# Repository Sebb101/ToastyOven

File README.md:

# ToastyOven
Custom PCBA Reflow Oven made from consumer toaster oven

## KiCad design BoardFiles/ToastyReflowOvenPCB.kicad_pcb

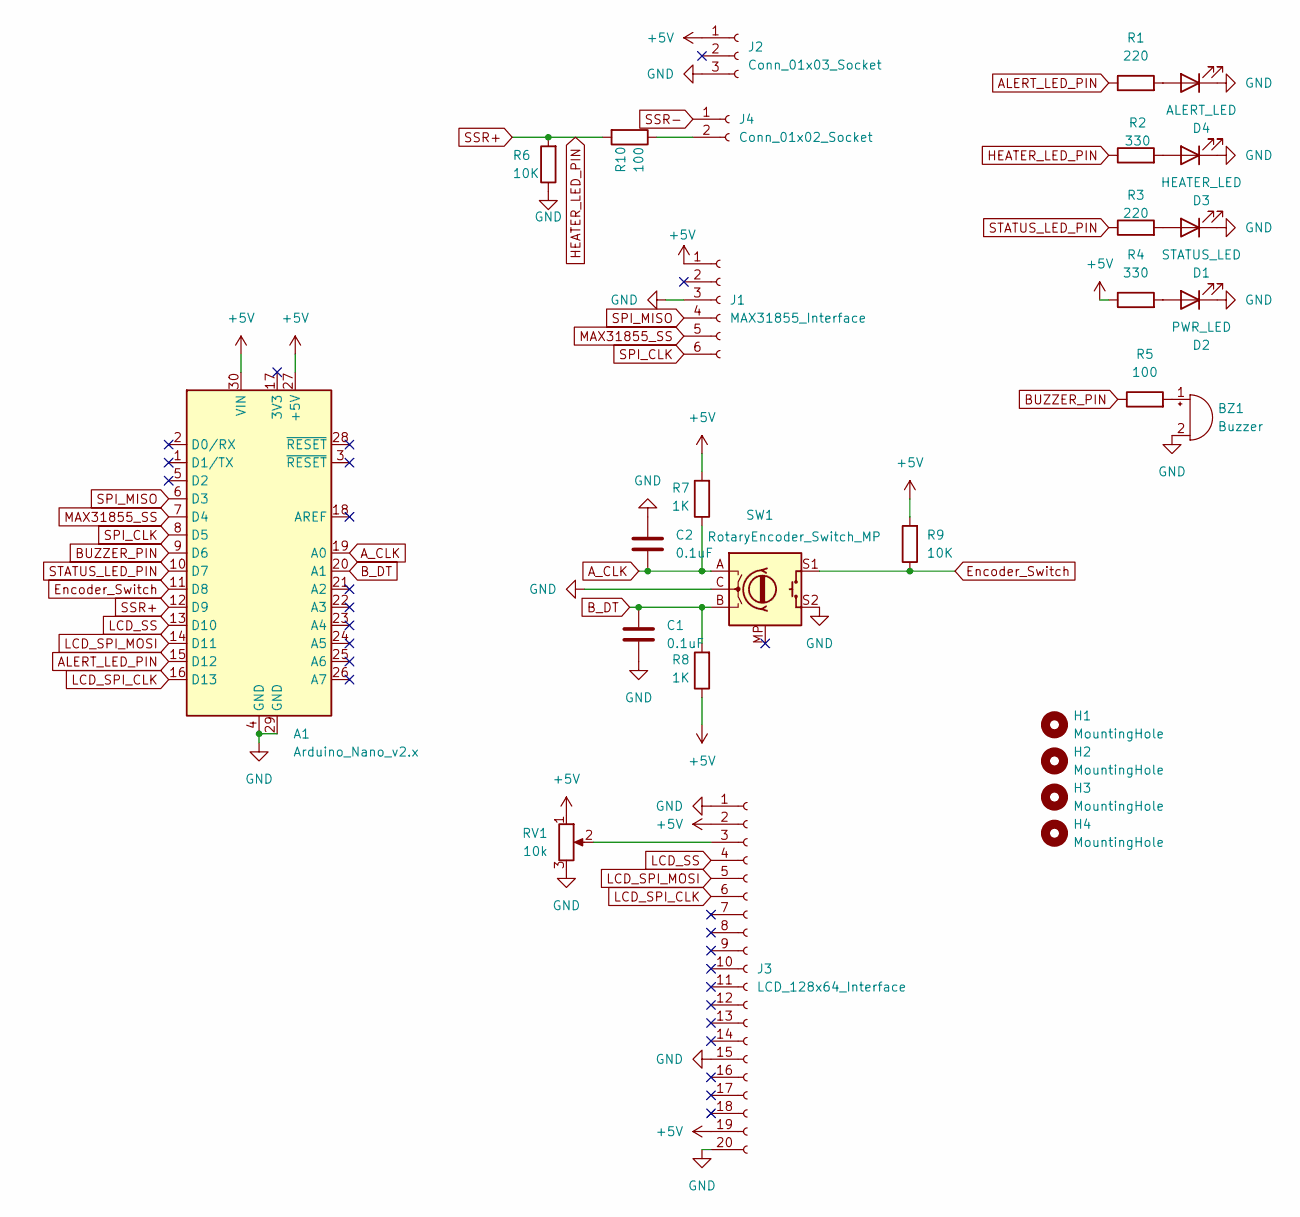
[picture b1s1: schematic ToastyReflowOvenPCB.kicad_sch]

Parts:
A1: Arduino_Nano_v2.x; Arduino_Nano
BZ1: Buzzer; Buzzer_12x9.5RM7.6
C1, C2: 0.1uF; C_Radial_D5.0mm_H7.0mm_P2.00mm
D1: STATUS_LED; LED_D5.0mm
D2: PWR_LED; LED_D5.0mm
D3: HEATER_LED; LED_D5.0mm
D4: ALERT_LED; LED_D5.0mm
H1, H2, H3, H4: MountingHole; MountingHole_3.2mm_M3
J1: MAX31855_Interface; PinHeader_1x06_P2.54mm_Vertical
J2: Conn_01x03_Socket; TerminalBlock_bornier-3_P5.08mm
J3: LCD_128x64_Interface; PinHeader_1x20_P2.54mm_Vertical
J4: Conn_01x02_Socket; TerminalBlock_bornier-2_P5.08mm
R1, R3: 220; R_Axial_DIN0207_L6.3mm_D2.5mm_P7.62mm_Horizontal
R2, R4: 330; R_Axial_DIN0207_L6.3mm_D2.5mm_P7.62mm_Horizontal
R5, R10: 100; R_Axial_DIN0207_L6.3mm_D2.5mm_P7.62mm_Horizontal
R6, R9: 10K; R_Axial_DIN0207_L6.3mm_D2.5mm_P7.62mm_Horizontal
R7, R8: 1K; R_Axial_DIN0207_L6.3mm_D2.5mm_P7.62mm_Horizontal
RV1: 10k; Potentiometer_ACP_CA9-V10_Vertical
SW1: RotaryEncoder_Switch_MP; RotaryEncoder_Alps_EC12E-Switch_Vertical_H20mm

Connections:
+5V: A1.27 (+5V), A1.30 (VIN), J1.1, J2.1, J3.2, J3.19, R4.1, R7.2, R8.1, R9.2, RV1.1
ALERT_LED_PIN: A1.15 (D12), R1.1
A_CLK: A1.19 (A0), C2.2, R7.1, SW1.A
BUZZER_PIN: A1.9 (D6), R5.1
B_DT: A1.20 (A1), C1.1, R8.2, SW1.B
Encoder_Switch: A1.11 (D8), R9.1, SW1.S1
GND: A1.4 (GND), A1.29 (GND), BZ1.2 (-), C1.2, C2.1, D1.1 (K), D2.1 (K), D3.1 (K), D4.1 (K), J1.3, J2.3, J3.1, J3.15, J3.20, R6.1, RV1.3, SW1.C, SW1.S2
HEATER_LED_PIN: A1.12 (D9), R2.1, R6.2, R10.2
LCD_SPI_CLK: A1.16 (D13), J3.6
LCD_SPI_MOSI: A1.14 (D11), J3.5
LCD_SS: A1.13 (D10), J3.4
MAX31855_SS: A1.7 (D4), J1.5
unnamed: BZ1.1 (+), R5.2
unnamed: D1.2 (A), R3.2
unnamed: D2.2 (A), R4.2
unnamed: D3.2 (A), R2.2
unnamed: D4.2 (A), R1.2
unnamed: J3.3, RV1.2
unnamed: J4.2, R10.1
SPI_CLK: A1.8 (D5), J1.6
SPI_MISO: A1.6 (D3), J1.4
SSR-: J4.1
STATUS_LED_PIN: A1.10 (D7), R3.1

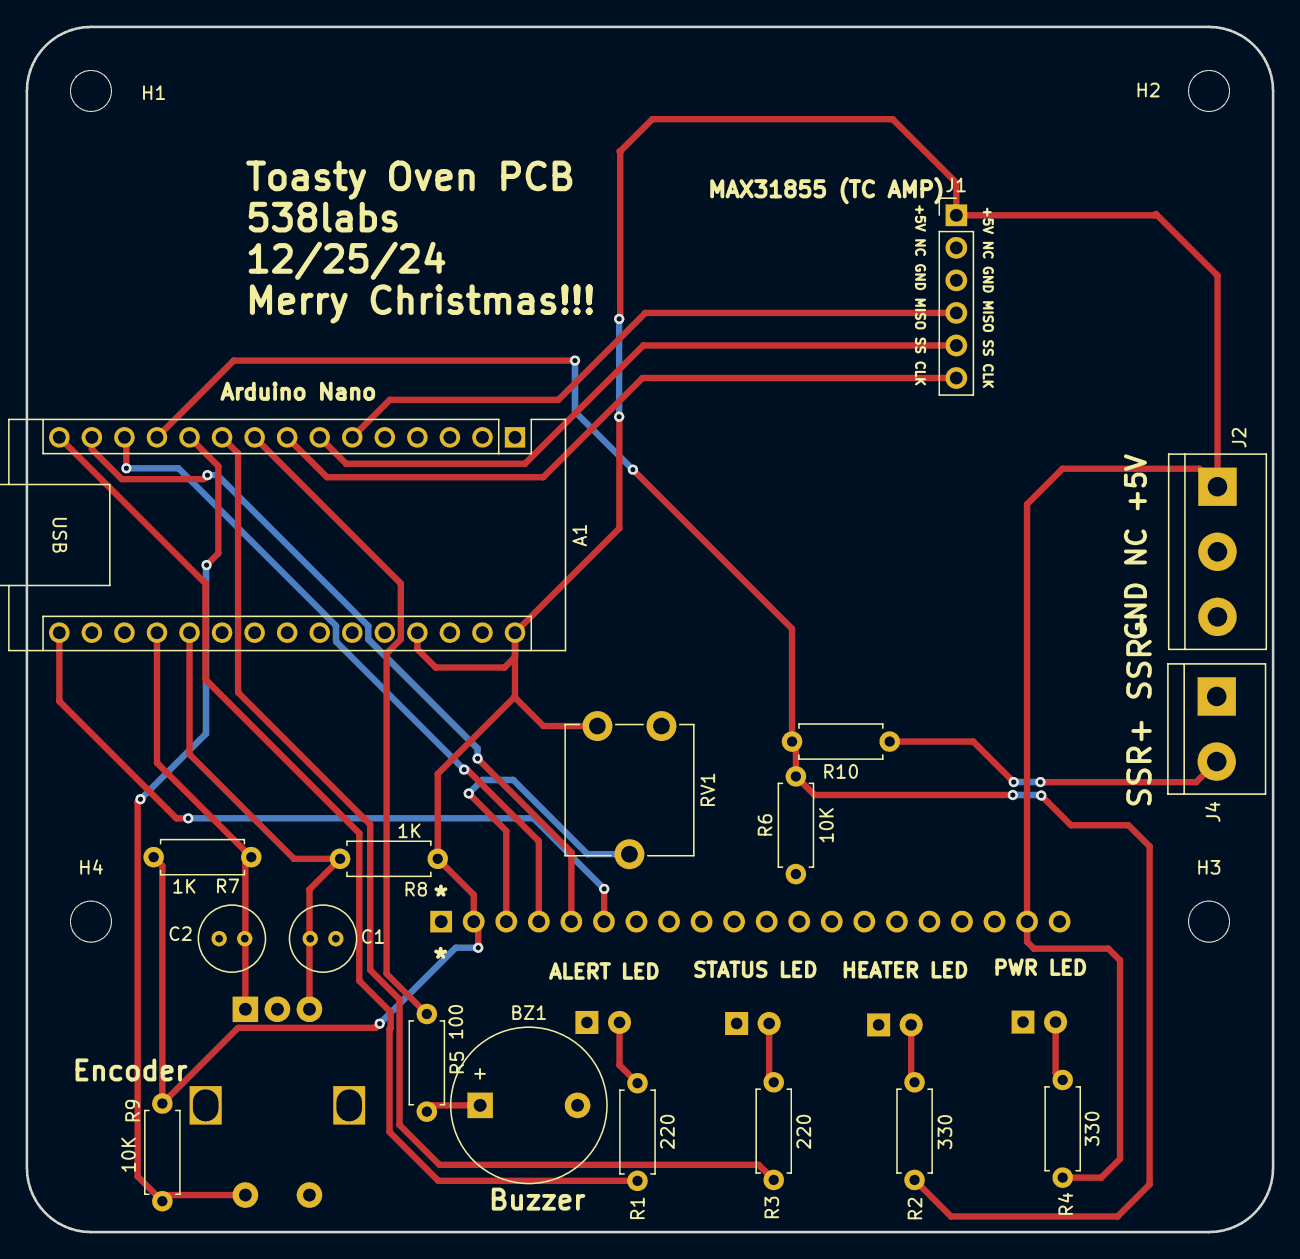
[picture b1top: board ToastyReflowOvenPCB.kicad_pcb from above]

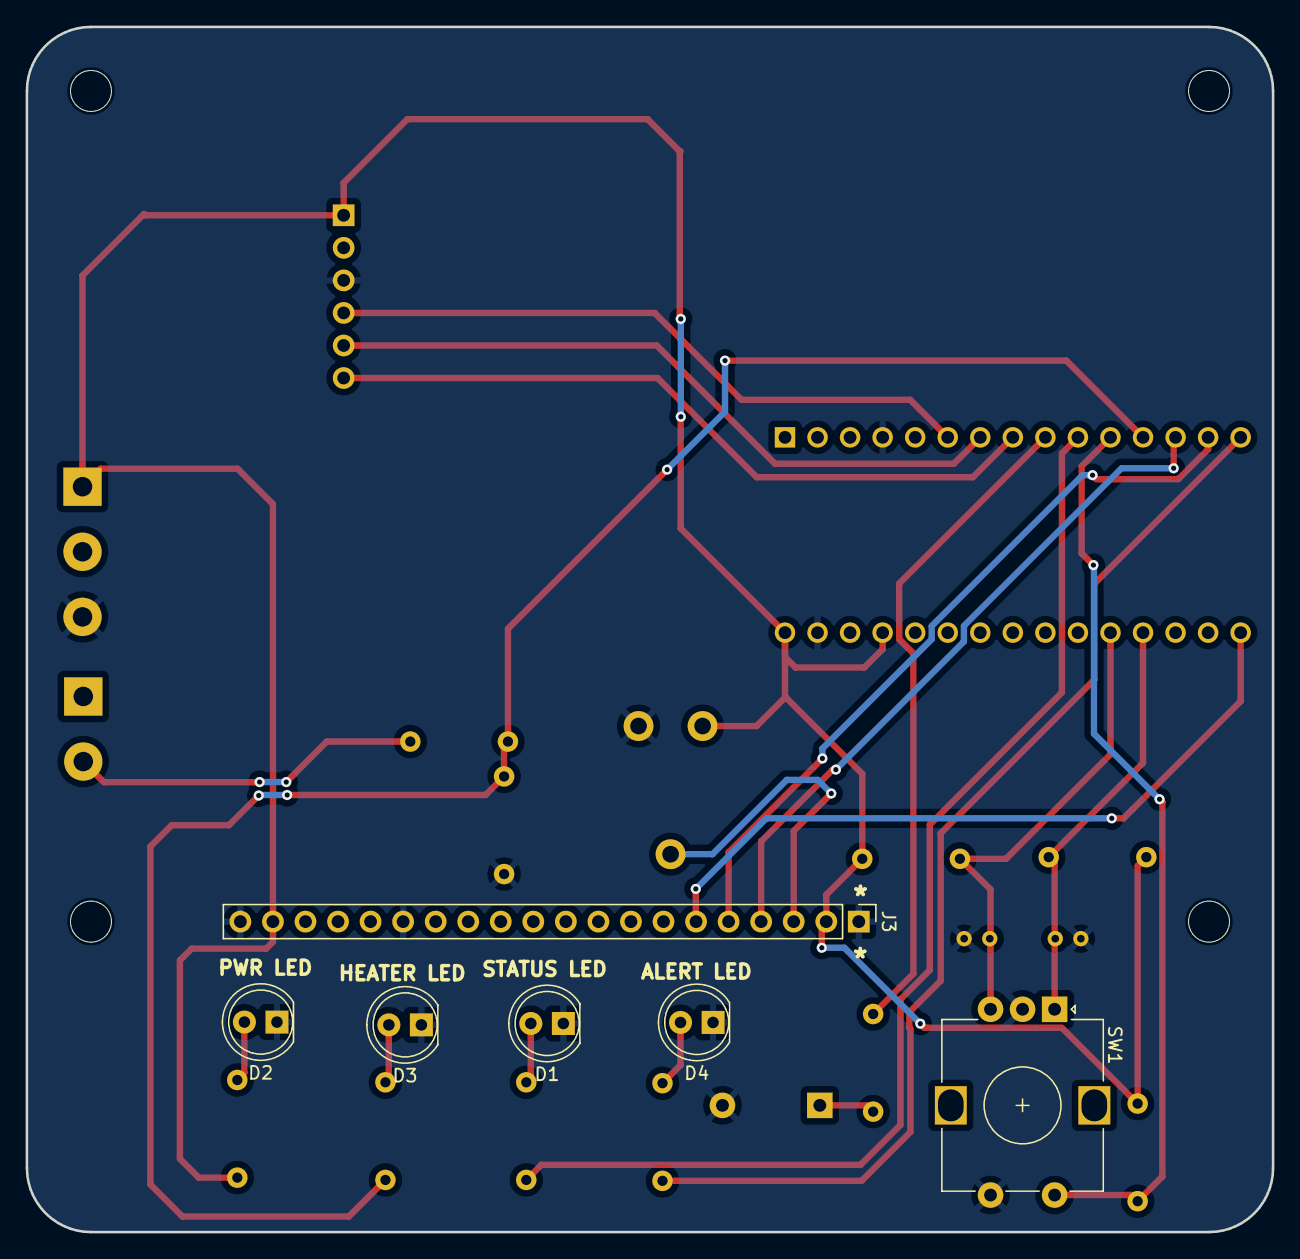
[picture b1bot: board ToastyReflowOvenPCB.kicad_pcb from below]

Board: 2 copper layers, 97.2 x 94.0 mm, 28 parts (6 on the bottom side), 22 nets.

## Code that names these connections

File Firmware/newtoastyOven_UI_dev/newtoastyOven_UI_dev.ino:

#include <Wire.h>
#include <Arduino.h>
#include <U8g2lib.h>
#include "Adafruit_MAX31855.h"
#include <SimpleRotary.h>
#include <PID_v1.h>  // Standard PID library for Arduino

// Pin Definitions
#define SSRpin 9
#define statusLEDpin 7
#define alertLEDpin 12
#define buzzerPin 6
#define A_CLK 15
#define B_DT 14
#define encoder_switch 8
#define MAXDO 3
#define MAXCS 4
#define MAXCLK 5

// Rotary Encoder
SimpleRotary rotary(A_CLK, B_DT, encoder_switch);

// Thermocouple Sensor
Adafruit_MAX31855 thermocouple(MAXCLK, MAXCS, MAXDO);

// PID Variables
double setTemp = 150.0;
double Input, Output;
double Kp = 3.5, Ki = 4.0, Kd = 1.2;
PID myPID(&Input, &Output, &setTemp, Kp, Ki, Kd, DIRECT);

// OLED Display (Optimized for Memory)
U8G2_SSD1306_128X64_NONAME_1_HW_I2C u8g2(U8G2_R0, /* clock=*/ SCL, /* data=*/ SDA, /* reset=*/ U8X8_PIN_NONE);

// Menu States
enum MenuState { MAIN_MENU, SET_TEMP, HEAT_MENU };
MenuState menu = MAIN_MENU;

// System Status
bool heating = false;
unsigned long startTime = 0;

void setup() {
    Serial.begin(115200);
    Serial.println(F("System Initialized..."));

    pinMode(buzzerPin, OUTPUT);
    pinMode(SSRpin, OUTPUT);
    pinMode(statusLEDpin, OUTPUT);
    pinMode(alertLEDpin, OUTPUT);
    digitalWrite(SSRpin, LOW);
    digitalWrite(statusLEDpin, LOW);
    digitalWrite(alertLEDpin, LOW);

    u8g2.begin();
    myPID.SetMode(AUTOMATIC);
}

void loop() {
    Input = thermocouple.readCelsius();
    myPID.Compute();

    if (heating) {
        digitalWrite(SSRpin, Output > 50 ? HIGH : LOW);
    } else {
        digitalWrite(SSRpin, LOW);
    }

    handleUserInput();
    displayUI();
}

// Handle Rotary Encoder Input
void handleUserInput() {
    int action = rotary.rotate();
    if (action == 1) {  
        if (menu == SET_TEMP) setTemp += 5;
    } else if (action == -1) {  
        if (menu == SET_TEMP) setTemp -= 5;
    }

    if (rotary.push()) {  
        if (menu == MAIN_MENU) {
            menu = SET_TEMP;
        } else if (menu == SET_TEMP) {
            menu = HEAT_MENU;
            heating = true;
            startTime = millis();
        } else if (menu == HEAT_MENU) {
            menu = MAIN_MENU;
            heating = false;
        }
    }
}

// Display UI
void displayUI() {
    u8g2.firstPage();
    do {
        if (menu == MAIN_MENU) {
            u8g2.setCursor(2, 10);
            u8g2.print("MAIN MENU");
            u8g2.setCursor(2, 30);
            u8g2.print("> Set Temp: "); u8g2.print(setTemp); u8g2.print("C");
        } else if (menu == SET_TEMP) {
            u8g2.setCursor(2, 10);
            u8g2.print("SET TEMP:");
            u8g2.setCursor(2, 30);
            u8g2.print(setTemp); u8g2.print(" C");
        } else if (menu == HEAT_MENU) {
            u8g2.setCursor(2, 10);
            u8g2.print("HEATING...");
            u8g2.setCursor(2, 30);
            u8g2.print("Target: "); u8g2.print(setTemp); u8g2.print("C");
            u8g2.setCursor(2, 40);
            u8g2.print("Current: "); u8g2.print(Input); u8g2.print("C");
            u8g2.setCursor(2, 50);
            u8g2.print("Time: "); u8g2.print((millis() - startTime) / 1000); u8g2.print("s");
        }
    } while (u8g2.nextPage());
}

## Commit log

2024-12-27 Update toastyOven_UI_dev.ino
    added config page and reflow page
2025-01-05 Update toastyOven_UI_dev.ino
    added reflow process graph but ran into dynamic ram issues must reduce
2025-09-16 Working ver
    Got rid of everything to have a stable working version
2025-09-23 New Reflow Profile
    Updated solder profile, experimented and reflowed first board with promising results
